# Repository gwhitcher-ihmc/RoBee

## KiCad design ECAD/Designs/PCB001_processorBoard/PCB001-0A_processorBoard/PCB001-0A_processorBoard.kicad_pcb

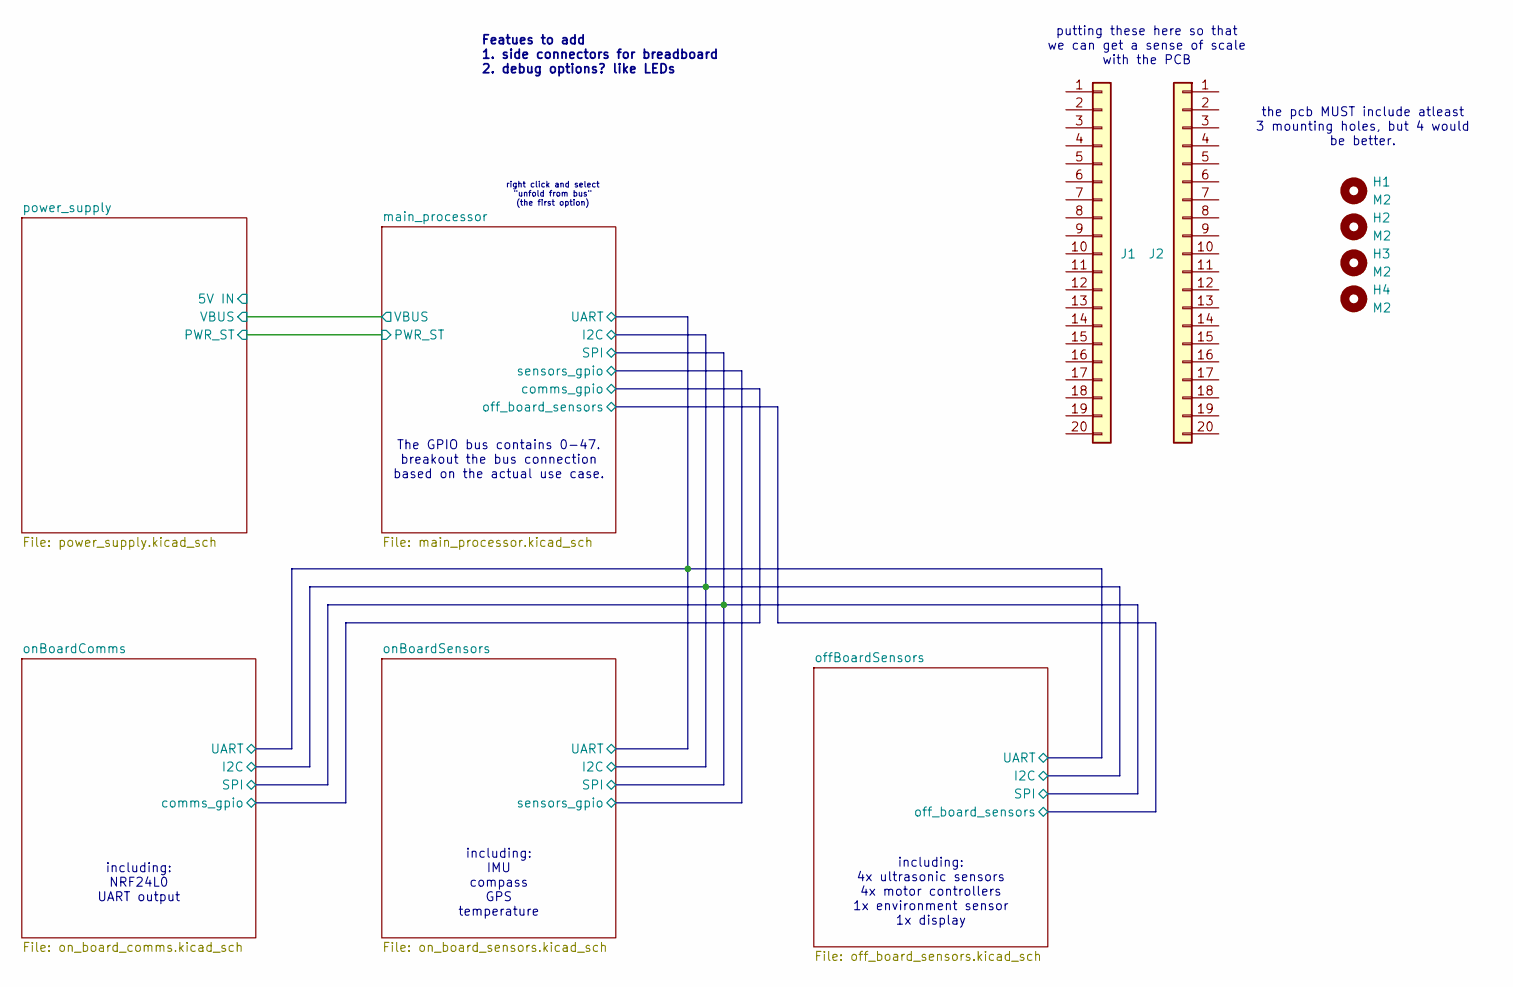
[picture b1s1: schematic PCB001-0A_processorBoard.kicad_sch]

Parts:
H1, H2, H3, H4: M2; MountingHole_2.2mm_M2
J1, J2: Conn_01x20; PinHeader_1x20_P2.54mm_Vertical

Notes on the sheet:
The GPIO bus contains 0-47. breakout the bus connection based on the actual use case.
Featues to add 1. side connectors for breadboard 2. debug options? like LEDs
including: 4x ultrasonic sensors 4x motor controllers 1x environment sensor 1x display
right click and select "unfold from bus" (the first option)
putting these here so that we can get a sense of scale with the PCB
including: IMU compass GPS temperature
the pcb MUST include atleast 3 mounting holes, but 4 would be better.
including: NRF24L0 UART output

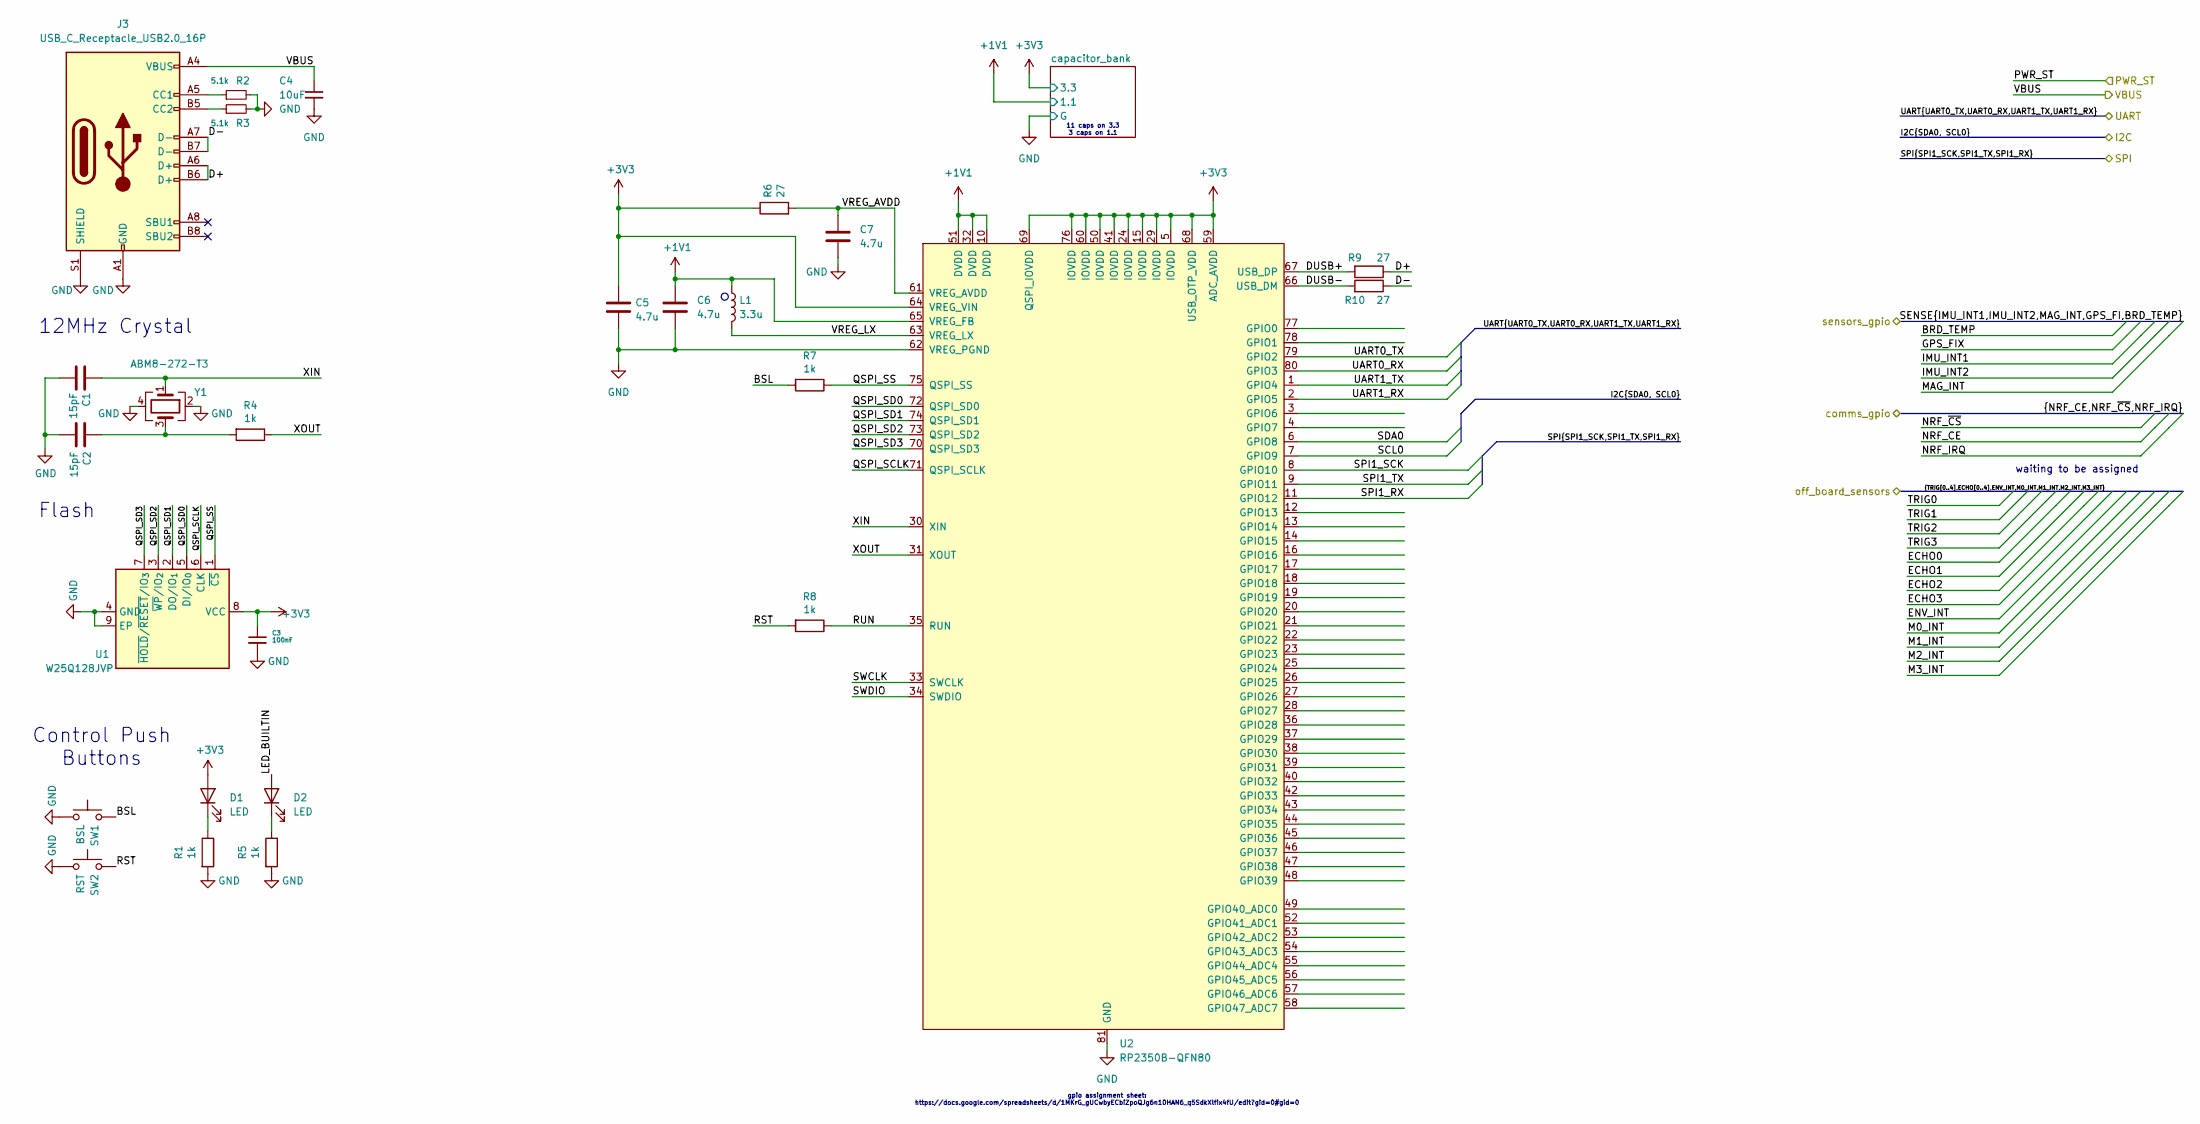
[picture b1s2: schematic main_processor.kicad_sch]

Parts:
C1, C2: 15pF; C_0402_1005Metric_Pad0.74x0.62mm_HandSolder; digikey 490-8080-2-ND
C3: 100nF; C_0402_1005Metric_Pad0.74x0.62mm_HandSolder
C4: 10uF; C_0603_1608Metric; digikey 1276-1038-2-ND
C5, C6, C7: 4.7u; C_0402_1005Metric_Pad0.74x0.62mm_HandSolder; digikey 1276-1482-2-ND
D1, D2: LED; LED_0805_2012Metric; digikey 160-1416-2-ND
J3: USB_C_Receptacle_USB2.0_16P; USB_C_Receptacle_GCT_USB4105-xx-A_16P_TopMnt_Horizontal; digikey 2223-UJ20-C-H-G-SMT-1-P16-TR-ND
L1: 3.3u; 3.3UH_inductor; digikey 535-AOTA-B201610S3R3-101-TTR-ND
R1, R4, R5, R7, R8: 1k; R_0402_1005Metric_Pad0.72x0.64mm_HandSolder; digikey 311-1.0KJRTR-ND
R2, R3: 5.1k; R_0402_1005Metric_Pad0.72x0.64mm_HandSolder; digikey 311-5.10KLRTR-ND
R6, R9, R10: 27; R_0402_1005Metric_Pad0.72x0.64mm_HandSolder; digikey 311-27JRTR-ND
SW1: BSL; SW_SPST_PTS647_Sx38; digikey PTS647SM38SMTR2LFSTR-ND
SW2: RST; SW_SPST_PTS647_Sx38; digikey PTS647SM38SMTR2LFSTR-ND
U1: W25Q128JVP; WSON-8-1EP_6x5mm_P1.27mm_EP3.4x4.3mm; digikey 256-W25Q128JVPIQTR-ND
U2: RP2350B-QFN80; RP2350B_QFN-80_EP_10.573x10.573_Pitch0.4mm
Y1: ABM8-272-T3; Crystal_SMD_3225-4Pin_3.2x2.5mm; digikey 535-ABM8-272-T3TR-ND

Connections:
+1V1: C6.1, L1.1, U2.10 (DVDD), U2.32 (DVDD), U2.51 (DVDD), U2.65 (VREG_FB); also elsewhere on the board
+3V3: C3.1, C5.1, D1.2 (A), R6.1, U1.8 (VCC), U2.5 (IOVDD), U2.15 (IOVDD), U2.24 (IOVDD), U2.29 (IOVDD), U2.41 (IOVDD), U2.50 (IOVDD), U2.59 (ADC_AVDD), U2.60 (IOVDD), U2.64 (VREG_VIN), U2.68 (USB_OTP_VDD), U2.69 (QSPI_IOVDD), U2.76 (IOVDD); also elsewhere on the board
/main_processor/BSL: R7.2, SW1.2
/main_processor/D+: J3.A6 (D+), J3.B6 (D+), R9.1
/main_processor/D-: J3.A7 (D-), J3.B7 (D-), R10.1
/main_processor/DUSB+: R9.2, U2.67 (USB_DP)
/main_processor/DUSB-: R10.2, U2.66 (USB_DM)
/main_processor/LED_BUILTIN: D2.2 (A)
/main_processor/QSPI_SCLK: U1.6 (CLK), U2.71 (QSPI_SCLK)
/main_processor/QSPI_SD0: U1.5 (DI/IO_{0}), U2.72 (QSPI_SD0)
/main_processor/QSPI_SD1: U1.2 (DO/IO_{1}), U2.74 (QSPI_SD1)
/main_processor/QSPI_SD2: U1.3 (~WP/IO_{2}), U2.73 (QSPI_SD2)
/main_processor/QSPI_SD3: U1.7 (~HOLD/~RESET/IO_{3}), U2.70 (QSPI_SD3)
/main_processor/QSPI_SS: R7.1, U1.1 (~CS), U2.75 (QSPI_SS)
/main_processor/RST: R8.2, SW2.2
/main_processor/RUN: R8.1, U2.35 (RUN)
/main_processor/SCL0: U2.7 (GPIO9)
/main_processor/SDA0: U2.6 (GPIO8)
/main_processor/SPI1_RX: U2.11 (GPIO12)
/main_processor/SPI1_SCK: U2.8 (GPIO10)
/main_processor/SPI1_TX: U2.9 (GPIO11)
/main_processor/SWCLK: U2.33 (SWCLK)
/main_processor/SWDIO: U2.34 (SWDIO)
/main_processor/UART0_RX: U2.80 (GPIO3)
/main_processor/UART0_TX: U2.79 (GPIO2)
/main_processor/UART1_RX: U2.2 (GPIO5)
/main_processor/UART1_TX: U2.1 (GPIO4)
/main_processor/VBUS: C4.1, J3.A4 (VBUS), J3.A9 (VBUS), J3.B4 (VBUS), J3.B9 (VBUS); also elsewhere on the board
/main_processor/VREG_AVDD: C7.1, R6.2, U2.61 (VREG_AVDD)
/main_processor/VREG_LX: L1.2, U2.63 (VREG_LX)
/main_processor/XIN: C1.1, U2.30 (XIN), Y1.1
/main_processor/XOUT: R4.1, U2.31 (XOUT)
GND: C1.2, C2.2, C3.2, C4.2, C5.2, C6.2, C7.2, J3.A1 (GND), J3.A12 (GND), J3.B1 (GND), J3.B12 (GND), J3.S1 (SHIELD), R1.2, R2.2, R3.2, R5.2, SW1.1, SW2.1, U1.4 (GND), U1.9 (EP), U2.62 (VREG_PGND), U2.81 (GND), Y1.2, Y1.4; also elsewhere on the board
unnamed: C2.1, R4.2, Y1.3
unnamed: D1.1 (K), R1.1
unnamed: D2.1 (K), R5.1
unnamed: J3.A5 (CC1), R2.1
unnamed: J3.B5 (CC2), R3.1

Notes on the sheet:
Flash
12MHz Crystal
Control Push Buttons
11 caps on 3.3 3 caps on 1.1
waiting to be assigned
gpio assignment sheet: https://docs.google.com/spreadsheets/d/1MKrG_gUCwbyECbiZpoQJg6n10HAN6_q5SdkXlfix4fU/edit?gid=0#gid=0

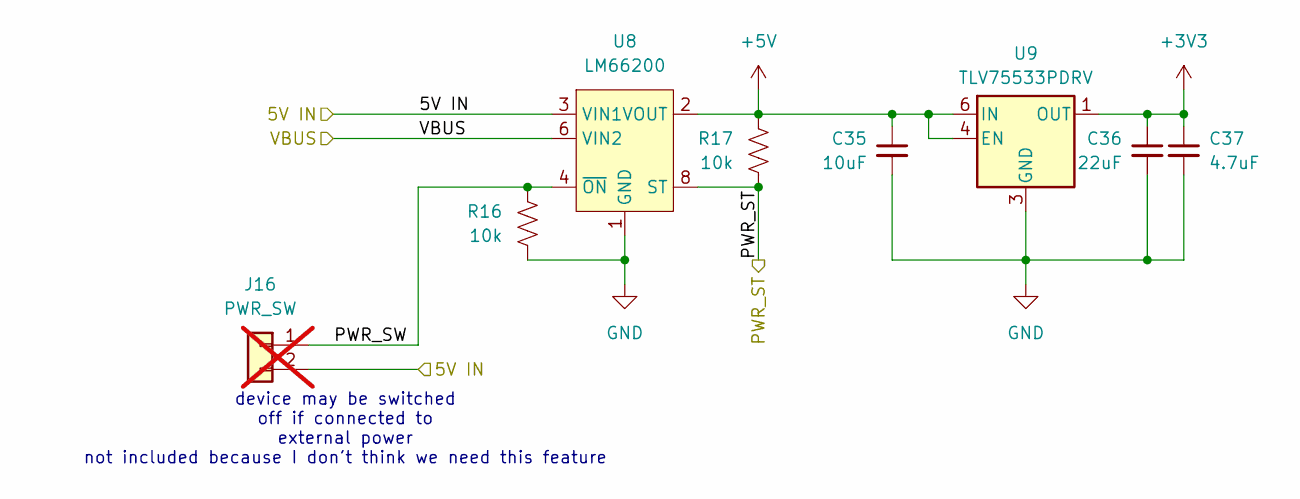
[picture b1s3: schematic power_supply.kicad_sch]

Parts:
C35: 10uF
C36: 22uF
C37: 4.7uF
J16: PWR_SW; JST_PH_B2B-PH-K_1x02_P2.00mm_Vertical; not fitted
R16, R17: 10k; R_0402_1005Metric_Pad0.72x0.64mm_HandSolder
U8: LM66200; SOT-583-8
U9: TLV75533PDRV; WSON-6-1EP_2x2mm_P0.65mm_EP1x1.6mm; digikey 296-51807-2-ND

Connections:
+3V3: C36.1, C37.1, U9.1 (OUT); also elsewhere on the board
+5V: C35.1, R17.1, U8.2 (VOUT), U8.7 (VOUT), U9.4 (EN), U9.6 (IN); also elsewhere on the board
/main_processor/PWR_ST: R17.2, U8.8 (ST)
/main_processor/VBUS: U8.6 (VIN2); also elsewhere on the board
/power_supply/5V IN: J16.2, U8.3 (VIN1)
/power_supply/PWR_SW: J16.1, R16.1, U8.4 (~ON)
GND: C35.2, C36.2, C37.2, R16.2, U8.1 (GND), U8.5 (GND), U9.3 (GND), U9.7 (GND); also elsewhere on the board

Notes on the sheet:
device may be switched off if connected to external power not included because I don't think we need this feature

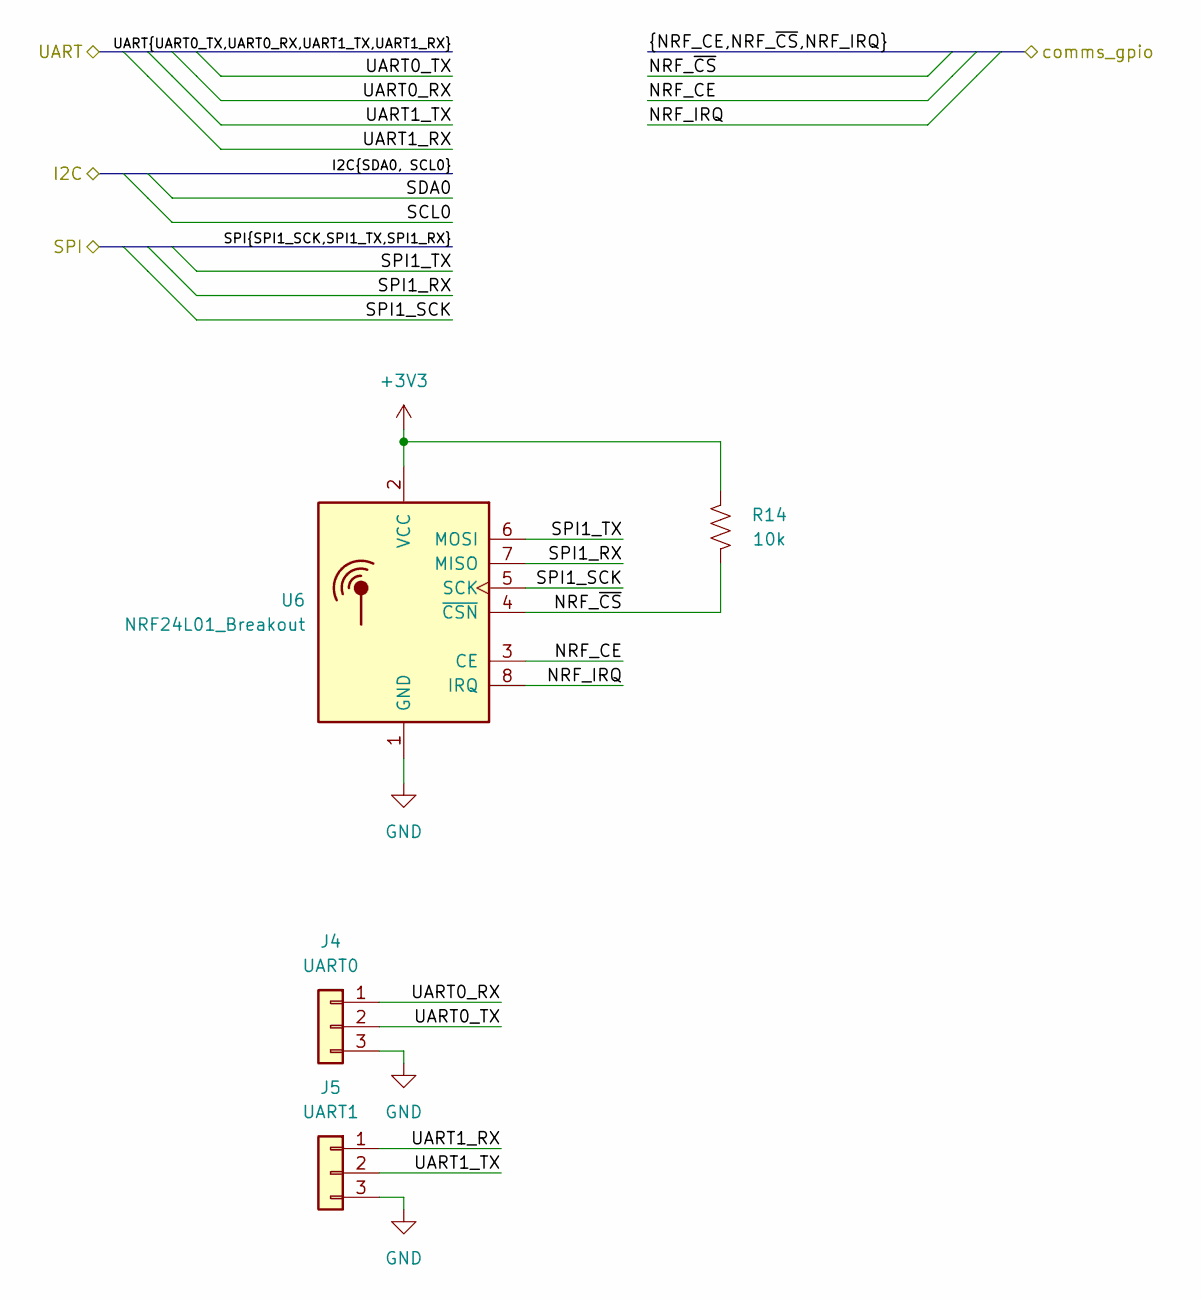
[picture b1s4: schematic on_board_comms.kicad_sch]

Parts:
J4: UART0; Molex_PicoBlade_53047-0310_1x03_P1.25mm_Vertical
J5: UART1; Molex_PicoBlade_53047-0310_1x03_P1.25mm_Vertical
R14: 10k; R_0402_1005Metric_Pad0.72x0.64mm_HandSolder
U6: NRF24L01_Breakout; nRF24L01_Breakout

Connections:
+3V3: R14.2, U6.2 (VCC); also elsewhere on the board
/main_processor/NRF_CE: U6.3 (CE)
/main_processor/NRF_IRQ: U6.8 (IRQ)
/main_processor/NRF_~CS: R14.1, U6.4 (~CSN)
/onBoardComms/SPI1_RX: U6.7 (MISO)
/onBoardComms/SPI1_SCK: U6.5 (SCK)
/onBoardComms/SPI1_TX: U6.6 (MOSI)
/onBoardComms/UART0_RX: J4.1
/onBoardComms/UART0_TX: J4.2
/onBoardComms/UART1_RX: J5.1
/onBoardComms/UART1_TX: J5.2
GND: J4.3, J5.3, U6.1 (GND); also elsewhere on the board

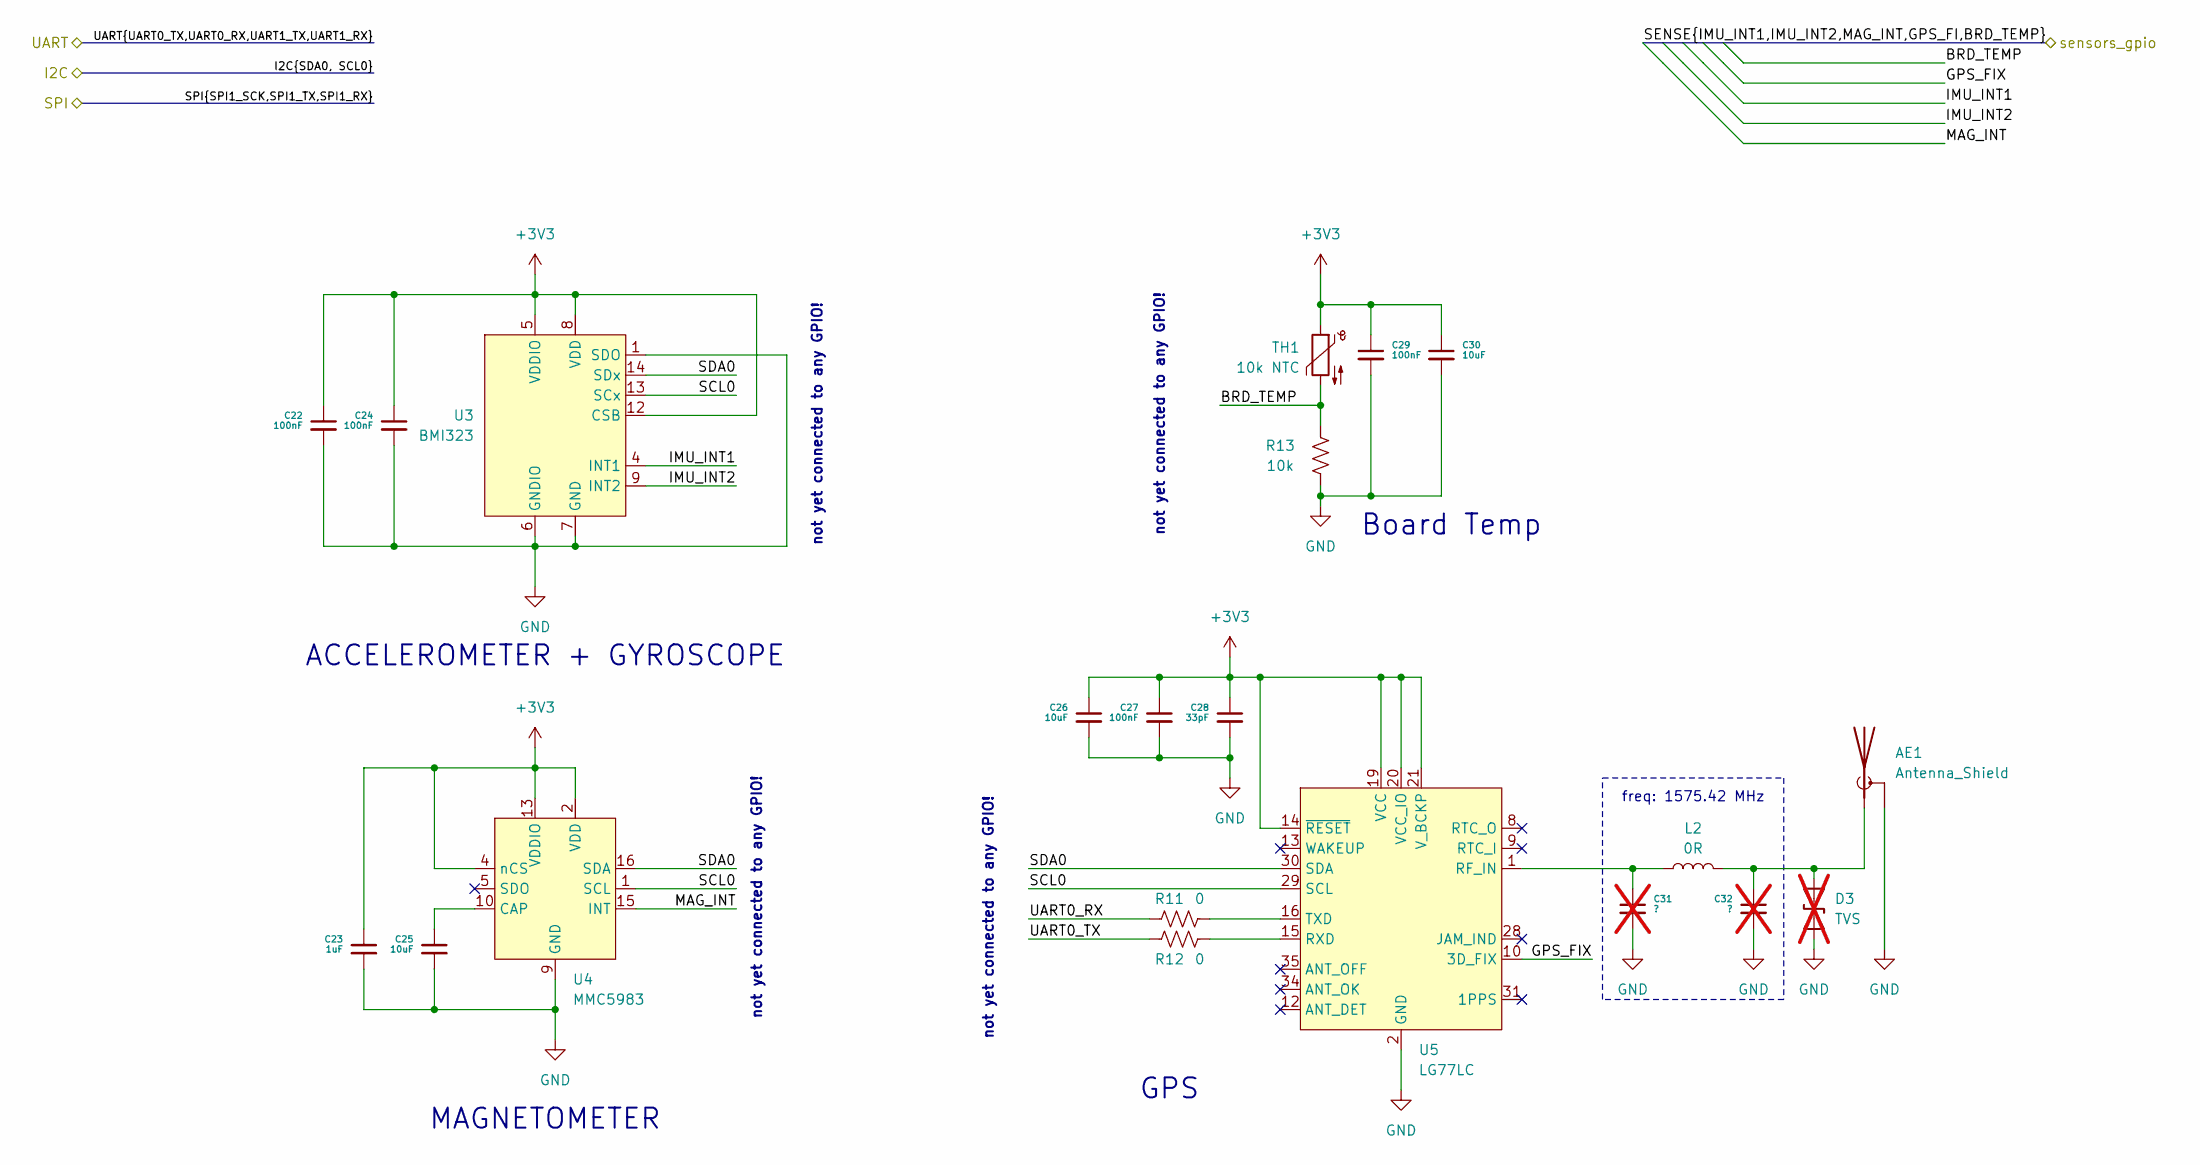
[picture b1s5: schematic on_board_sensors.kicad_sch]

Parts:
AE1: Antenna_Shield; U.FL_Molex_MCRF_73412-0110_Vertical
C22, C24, C27, C29: 100nF; C_0402_1005Metric_Pad0.74x0.62mm_HandSolder
C23: 1uF; C_0402_1005Metric_Pad0.74x0.62mm_HandSolder
C25, C26, C30: 10uF; C_0805_2012Metric
C28: 33pF; C_0402_1005Metric_Pad0.74x0.62mm_HandSolder
C31, C32: ?; C_0402_1005Metric_Pad0.74x0.62mm_HandSolder; not fitted
D3: TVS; D_DO-201AE_P15.24mm_Horizontal; not fitted
L2: 0R; L_0402_1005Metric_Pad0.77x0.64mm_HandSolder
R11, R12: 0; R_0402_1005Metric_Pad0.72x0.64mm_HandSolder
R13: 10k; R_0402_1005Metric_Pad0.72x0.64mm_HandSolder
TH1: 10k NTC; R_0402_1005Metric_Pad0.72x0.64mm_HandSolder; digikey 445-2550-2-ND
U3: BMI323; 14-VFLGA; digikey 828-BMI323TR-ND
U4: MMC5983; MMC5983-16LGA
U5: LG77LC; LG77L_QWS; digikey 2958-LG77LICMDTR-ND

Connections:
+3V3: C22.1, C23.1, C24.1, C26.1, C27.1, C28.1, C29.1, C30.1, TH1.1, U3.5 (VDDIO), U3.8 (VDD), U3.12 (CSB), U4.2 (VDD), U4.4 (nCS), U4.13 (VDDIO), U5.14 (~RESET), U5.19 (VCC), U5.20 (VCC_IO), U5.21 (V_BCKP); also elsewhere on the board
/onBoardSensors/BRD_TEMP: R13.2, TH1.2
/onBoardSensors/GPS_FIX: U5.10 (3D_FIX)
/onBoardSensors/IMU_INT1: U3.4 (INT1)
/onBoardSensors/IMU_INT2: U3.9 (INT2)
/onBoardSensors/MAG_INT: U4.15 (INT)
/onBoardSensors/SCL0: U3.13 (SCx), U4.1 (SCL), U5.29 (SCL)
/onBoardSensors/SDA0: U3.14 (SDx), U4.16 (SDA), U5.30 (SDA)
/onBoardSensors/UART0_RX: R11.1
/onBoardSensors/UART0_TX: R12.1
GND: AE1.2 (Shield), C22.2, C23.2, C24.2, C25.2, C26.2, C27.2, C28.2, C29.2, C30.2, C31.2, C32.2, R13.1, U3.1 (SDO), U3.6 (GNDIO), U3.7 (GND), U4.9 (GND), U4.11 (GND), U5.2 (GND), U5.18 (GND), U5.37 (GND), U5.38 (GND), U5.39 (GND), U5.40 (GND), U5.41 (GND), U5.42 (GND), U5.43 (GND); also elsewhere on the board
unnamed: AE1.1 (A), C32.1, D3.2 (A2), L2.2
unnamed: U3.2 (NC), U3.3 (NC), U3.10 (NC), U3.11 (NC)
unnamed: C25.1, U4.10 (CAP)
unnamed: U4.3 (NC), U4.6 (NC), U4.7 (NC), U4.8 (NC), U4.12 (NC), U4.14 (NC)
unnamed: C31.1, L2.1, U5.1 (RF_IN)
unnamed: R12.2, U5.15 (RXD)
unnamed: R11.2, U5.16 (TXD)

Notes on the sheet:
not yet connected to any GPIO!
freq: 1575.42 MHz
MAGNETOMETER
ACCELEROMETER + GYROSCOPE
GPS
Board Temp

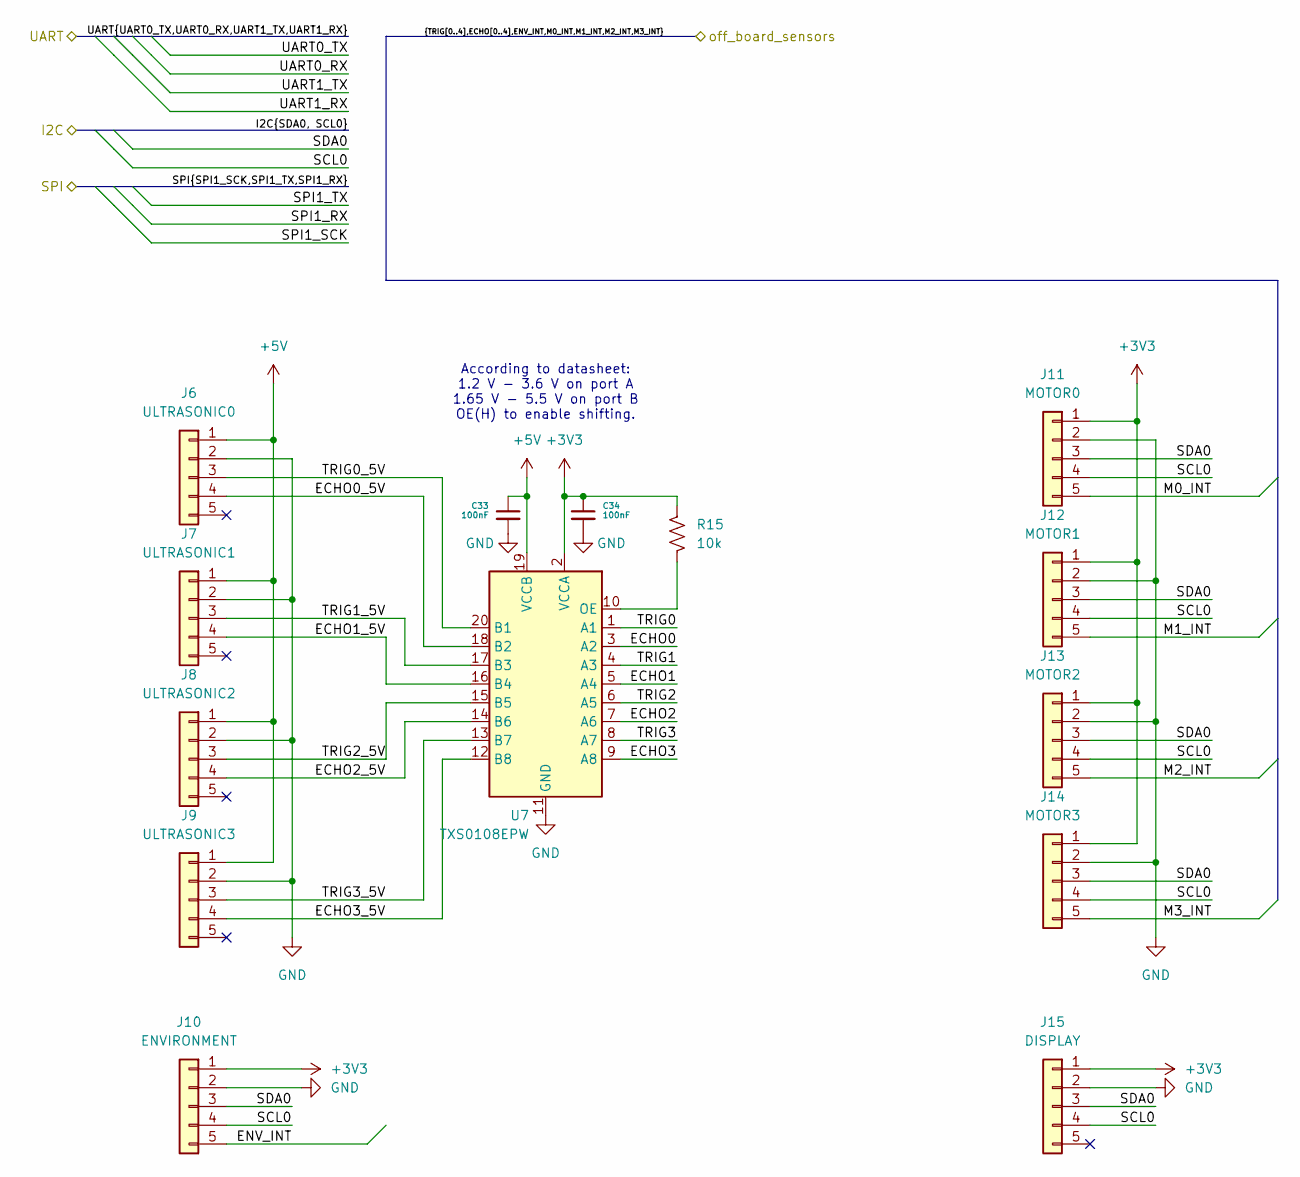
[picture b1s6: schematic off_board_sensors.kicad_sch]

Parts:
C33, C34: 100nF; C_0402_1005Metric_Pad0.74x0.62mm_HandSolder
J6: ULTRASONIC0; Molex_PicoBlade_53047-0510_1x05_P1.25mm_Vertical
J7: ULTRASONIC1; Molex_PicoBlade_53047-0510_1x05_P1.25mm_Vertical
J8: ULTRASONIC2; Molex_PicoBlade_53047-0510_1x05_P1.25mm_Vertical
J9: ULTRASONIC3; Molex_PicoBlade_53047-0510_1x05_P1.25mm_Vertical
J10: ENVIRONMENT; Molex_PicoBlade_53047-0510_1x05_P1.25mm_Vertical
J11: MOTOR0; Molex_PicoBlade_53047-0510_1x05_P1.25mm_Vertical
J12: MOTOR1; Molex_PicoBlade_53047-0510_1x05_P1.25mm_Vertical
J13: MOTOR2; Molex_PicoBlade_53047-0510_1x05_P1.25mm_Vertical
J14: MOTOR3; Molex_PicoBlade_53047-0510_1x05_P1.25mm_Vertical
J15: DISPLAY; Molex_PicoBlade_53047-0510_1x05_P1.25mm_Vertical
R15: 10k; R_0402_1005Metric_Pad0.72x0.64mm_HandSolder
U7: TXS0108EPW; TSSOP-20_4.4x6.5mm_P0.65mm; digikey 296-21527-2-ND

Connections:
+3V3: C34.1, J10.1, J11.1, J12.1, J13.1, J14.1, J15.1, R15.1, U7.2 (VCCA); also elsewhere on the board
+5V: C33.1, J6.1, J7.1, J8.1, J9.1, U7.19 (VCCB); also elsewhere on the board
/main_processor/ECHO0: U7.3 (A2)
/main_processor/ECHO1: U7.5 (A4)
/main_processor/ECHO2: U7.7 (A6)
/main_processor/ECHO3: U7.9 (A8)
/main_processor/ENV_INT: J10.5
/main_processor/M0_INT: J11.5
/main_processor/M1_INT: J12.5
/main_processor/M2_INT: J13.5
/main_processor/M3_INT: J14.5
/main_processor/TRIG0: U7.1 (A1)
/main_processor/TRIG1: U7.4 (A3)
/main_processor/TRIG2: U7.6 (A5)
/main_processor/TRIG3: U7.8 (A7)
/offBoardSensors/ECHO0_5V: J6.4, U7.18 (B2)
/offBoardSensors/ECHO1_5V: J7.4, U7.16 (B4)
/offBoardSensors/ECHO2_5V: J8.4, U7.14 (B6)
/offBoardSensors/ECHO3_5V: J9.4, U7.12 (B8)
/offBoardSensors/SCL0: J10.4, J11.4, J12.4, J13.4, J14.4, J15.4
/offBoardSensors/SDA0: J10.3, J11.3, J12.3, J13.3, J14.3, J15.3
/offBoardSensors/TRIG0_5V: J6.3, U7.20 (B1)
/offBoardSensors/TRIG1_5V: J7.3, U7.17 (B3)
/offBoardSensors/TRIG2_5V: J8.3, U7.15 (B5)
/offBoardSensors/TRIG3_5V: J9.3, U7.13 (B7)
GND: C33.2, C34.2, J6.2, J7.2, J8.2, J9.2, J10.2, J11.2, J12.2, J13.2, J14.2, J15.2, U7.11 (GND); also elsewhere on the board
unnamed: R15.2, U7.10 (OE)

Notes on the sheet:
According to datasheet: 1.2 V - 3.6 V on port A 1.65 V - 5.5 V on port B OE(H) to enable shifting.

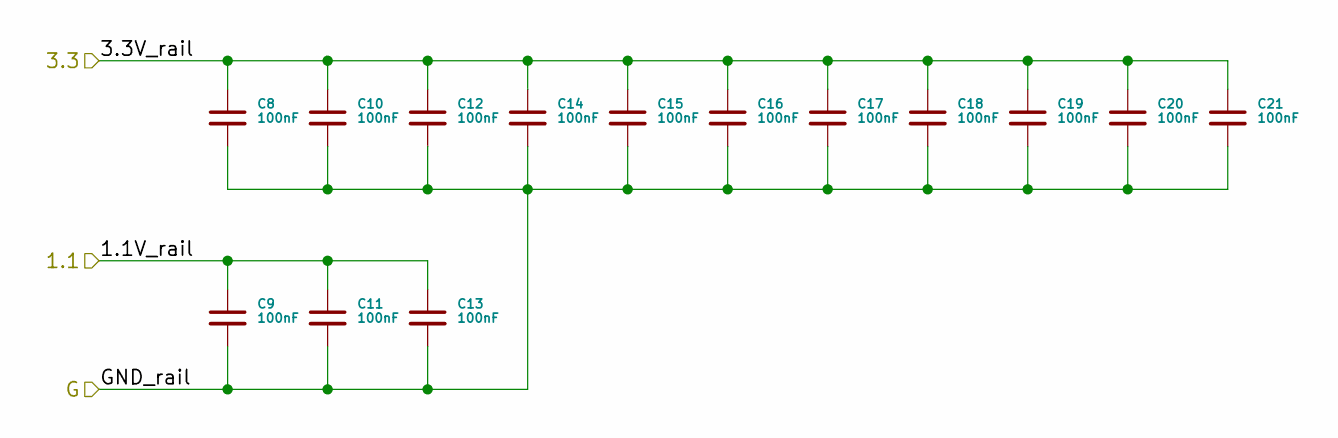
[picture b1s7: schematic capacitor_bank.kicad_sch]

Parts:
C8, C9, C10, C11, C12, C13, C14, C15, C16, C17, C18, C19, C20, C21: 100nF; C_0402_1005Metric_Pad0.74x0.62mm_HandSolder

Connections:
+1V1: C9.1, C11.1, C13.1; also elsewhere on the board
+3V3: C8.1, C10.1, C12.1, C14.1, C15.1, C16.1, C17.1, C18.1, C19.1, C20.1, C21.1; also elsewhere on the board
GND: C8.2, C9.2, C10.2, C11.2, C12.2, C13.2, C14.2, C15.2, C16.2, C17.2, C18.2, C19.2, C20.2, C21.2; also elsewhere on the board

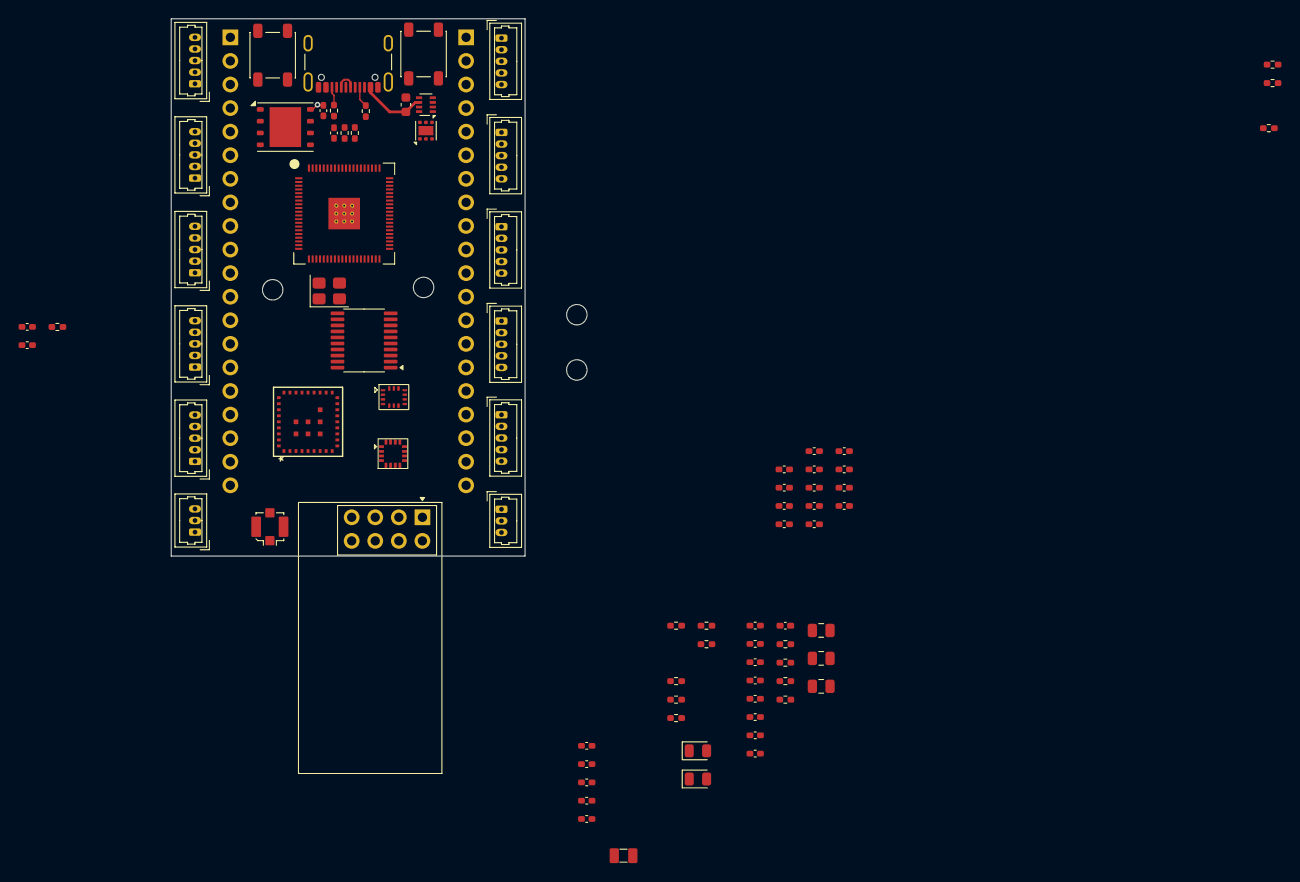
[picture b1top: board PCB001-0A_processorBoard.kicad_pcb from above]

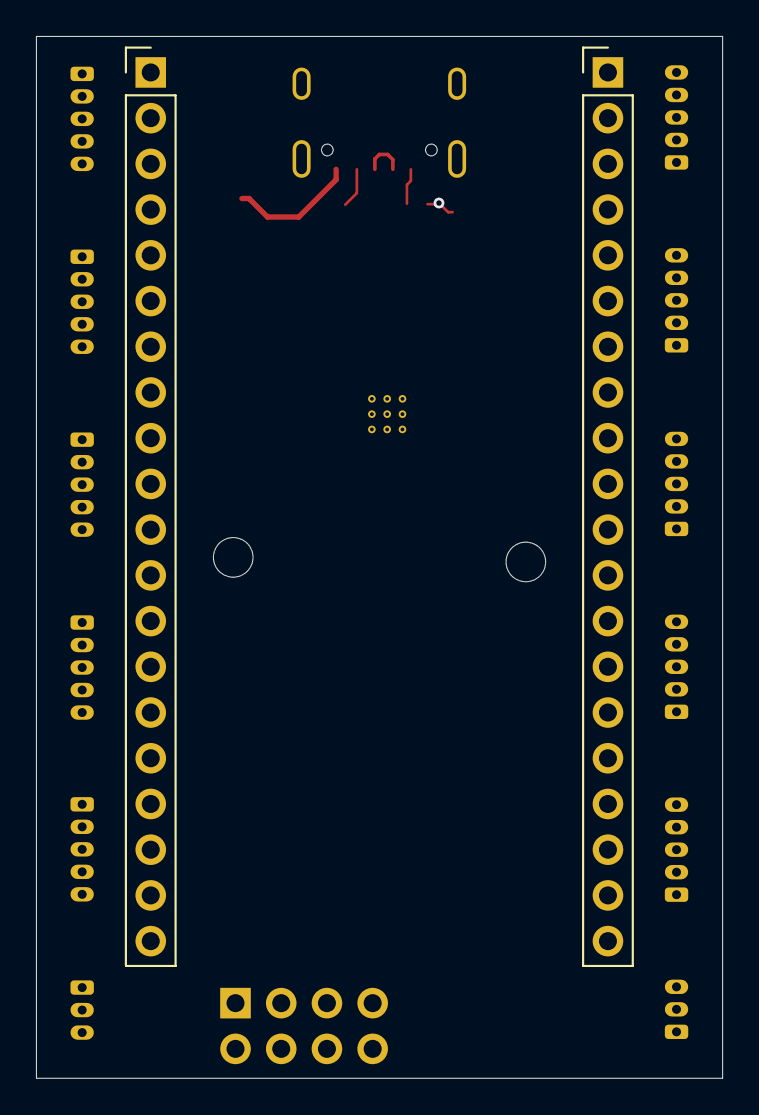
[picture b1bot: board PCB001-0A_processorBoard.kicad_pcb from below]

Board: 4 copper layers, 38.1 x 57.9 mm, 88 parts (2 on the bottom side), 51 nets.

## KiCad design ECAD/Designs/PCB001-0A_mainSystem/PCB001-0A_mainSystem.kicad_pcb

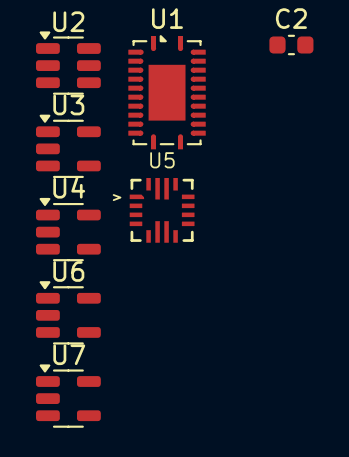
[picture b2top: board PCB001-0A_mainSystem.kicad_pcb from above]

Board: 2 copper layers, 8 parts (0 on the bottom side), 7 nets, no tracks yet.

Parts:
C2: C_Small; C_0603_1608Metric
U1: BQ24133RGY; Texas_RGY_R-PVQFN-N24_EP2.05x3.1mm
U2: TPS54302; SOT-23-6
U3, U4: MIC5504-3.3YM5; SOT-23-5
U5: MP28167GQ-A-P; 16-PowerVQFN
U6: INA180A2; SOT-23-5
U7: INA180A3; SOT-23-5

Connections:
+3.3VA: U4.5 (VOUT), U6.5 (V+), U7.5 (V+)
+5V: U3.1 (VIN), U4.1 (VIN), U7.4 (-)
/Power Supply/12V_OUT: U5.12 (OUT), U6.3 (+)
GND: U2.1 (GND), U3.2 (GND), U4.2 (GND), U5.2 (GND), U5.10 (AGND), U5.11 (GND), U6.2 (GND), U7.2 (GND)
unnamed: U1.22 (PGND), U1.23 (PGND)
unnamed: U1.2 (PVCC), U1.3 (PVCC)
unnamed: U1.1 (SW), U1.24 (SW)

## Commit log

2025-07-25 corrected file structure
2025-07-25 began work on power supply/added power supply block diagram
2025-07-25 added block diagrams and notes for motor controller
2025-07-30 new text file
2025-07-31 regular update
2025-07-31 made a new plan
2025-08-02 added project wants document to talk about some of my planning stuff that I want to do
2025-08-02 test
2025-08-02 fixed the gitignore file
2025-08-02 re-organized file structure in reports
2025-08-02 began work on a excel spreadsheet to plan and track pcb designs
2025-08-11 added processor board and upadted libraries
2025-08-11 moved pcb part tracking to google drive
2025-08-12 added off board sensors page, included more gpio (see google drive), and tracked the gpio better
2025-08-13 added a text file explaining how to set up kicad paths and libraries to make them more portable
2025-08-13 updated PCB001 files
2025-08-13 added more connectors to the side of the PCB, added a basic power supply, and began putting parts on the PCB.
2025-08-16 updated schematics
